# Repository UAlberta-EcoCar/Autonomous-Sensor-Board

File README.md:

# Autonomous-Sensor-Board
Connects Autonomous Sensors to the Jetson TX2 Board

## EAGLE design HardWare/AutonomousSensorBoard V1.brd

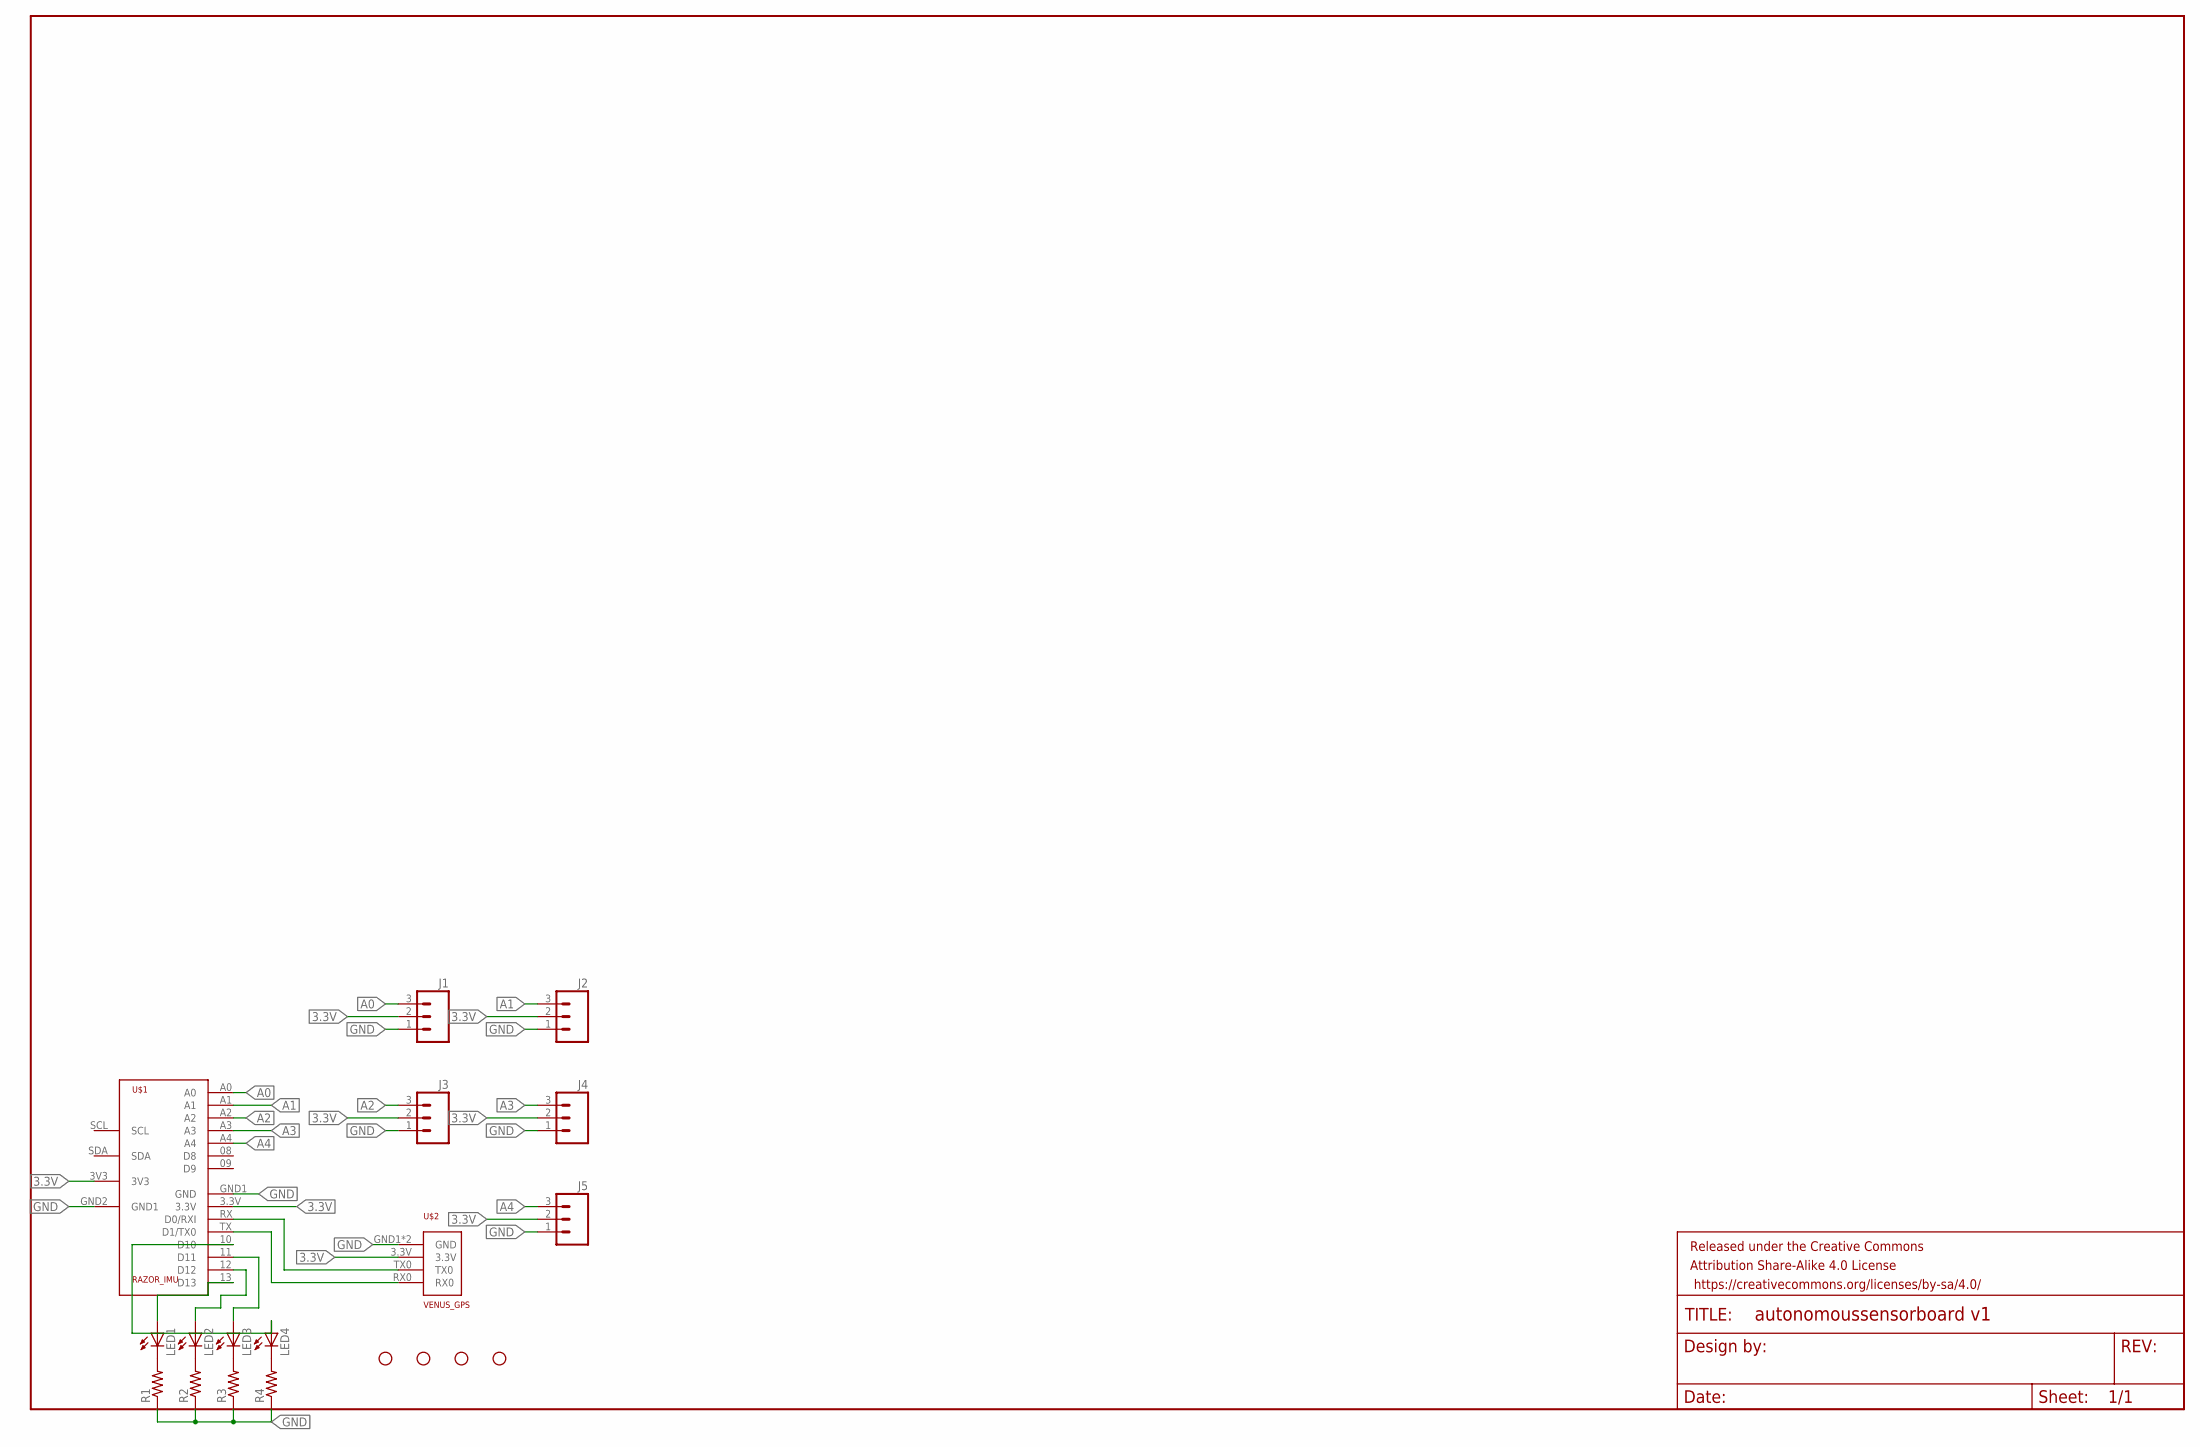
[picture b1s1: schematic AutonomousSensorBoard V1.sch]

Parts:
FRAME1: FRAME-LEDGER; CREATIVE_COMMONS
H1, H2, H3, H4: STAND-OFF
J1, J2, J3, J4, J5: M03LOCK; 1X03_LOCK
LED1, LED2, LED3, LED4: LEDCHIP-LED0805; CHIP-LED0805
R1, R2, R3, R4: R-US_M0805; M0805
U$1: RAZOR_IMU
U$2: VENUS_GPS

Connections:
3.3V: J1.2, J2.2, J3.2, J4.2, J5.2, U$1.3.3V, U$1.3V3, U$2.3.3V
A0: J1.3, U$1.A0
A1: J2.3, U$1.A1
A2: J3.3, U$1.A2
A3: J4.3, U$1.A3
A4: J5.3, U$1.A4
GND: J1.1, J2.1, J3.1, J4.1, J5.1, R1.1, R2.1, R3.1, R4.1, U$1.GND1 (GND), U$1.GND2 (GND1), U$2.GND1 (GND), U$2.GND2 (GND)
unnamed: U$1.RX (D0/RXI), U$2.TX0
unnamed: U$1.TX (D1/TX0), U$2.RX0
unnamed: LED1.C, R1.2
unnamed: LED2.C, R2.2
unnamed: LED4.C, R4.2
unnamed: LED3.C, R3.2
unnamed: LED2.A, U$1.12 (D12)
unnamed: LED1.A, U$1.13 (D13)
unnamed: LED3.A, U$1.11 (D11)
unnamed: LED4.A, U$1.10 (D10)

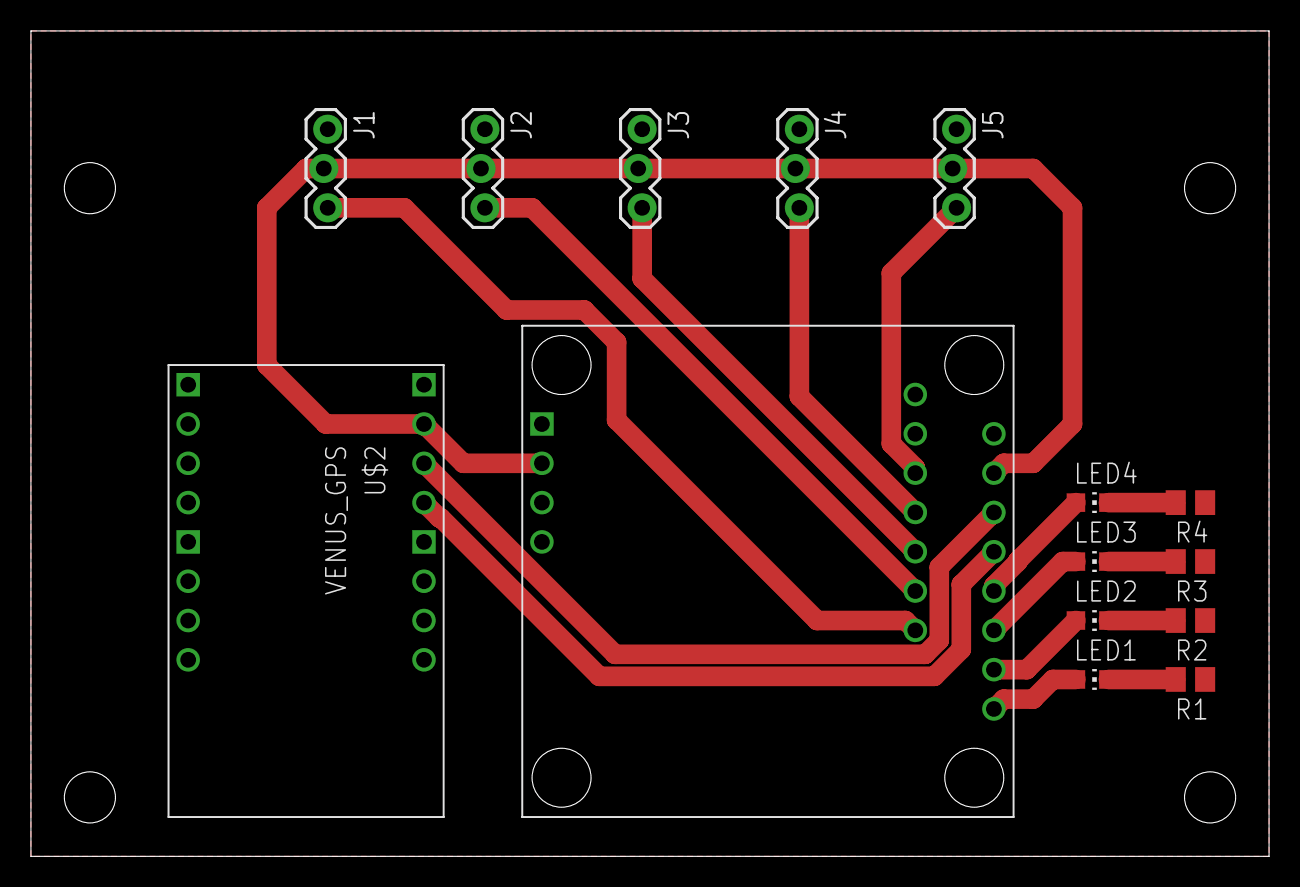
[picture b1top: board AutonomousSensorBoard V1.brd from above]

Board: 2 copper layers, 80.0 x 53.3 mm, 20 parts (0 on the bottom side), 17 nets.

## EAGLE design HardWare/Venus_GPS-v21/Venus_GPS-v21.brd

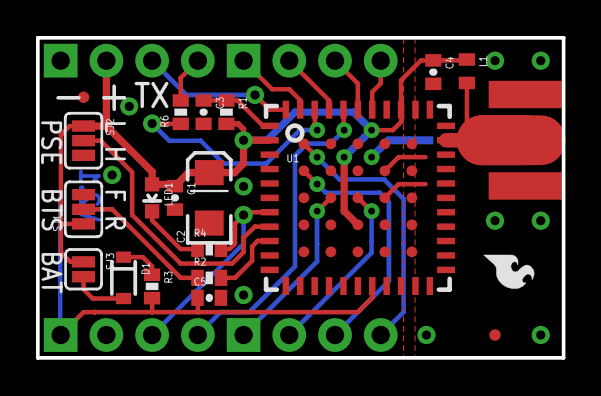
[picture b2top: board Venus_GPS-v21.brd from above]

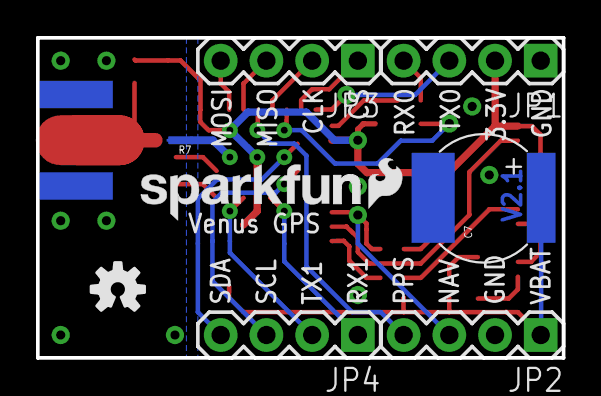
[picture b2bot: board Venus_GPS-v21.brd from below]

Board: 2 copper layers, 29.2 x 17.8 mm, 31 parts (9 on the bottom side), 25 nets.

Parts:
C1, C5: 0.1uF; 0402-CAP
C2: 10uF; EIA3216
C3: 1uF; 0402-CAP
C4: 22pF; 0402-CAP
C7: DNP; EN_J2
D1: BAS16; SOD-323
JP1: MAIN; 1X04
JP2: MISC; 1X04
JP3: SPI; 1X04
JP4: AUX; 1X04
JP5: SMA_EDGE; SMA-EDGE
JP6, JP7: FIDUCIALUFIDUCIAL; MICRO-FIDUCIAL
L1: 33nH; C0402
LED1: Red; LED-0603
LOGO1, LOGO2: LOGO-SFESK; SFE-LOGO-FLAME
LOGO3: LOGO-SFENW2; SFE-NEW-WEB
R1: 33k; 0402-RES
R2: 10k; 0402-RES
R3, R4: 330; 0402-RES
R6: 10K; 0402-RES
R7: 0; GND-JUMP
SJ1: BTS; SJ_3_PASTE2&3
SJ2: PSE; SJ_3_PASTE2&3
SJ3: BAT; SJ_2S
U1: VENUS638FLPX-L; VENUS638FLPX
U$4: OSHW-LOGOS; OSHW-LOGO-S
U$5: CREATIVE_COMMONS

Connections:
3.3V: C1.1, C2.A, C4.1, JP1.2, L1.1, LED1.A, R1.2, SJ1.1, SJ2.1, SJ3.1, U1.2, U1.36, U1.58
ANT: JP5.SIG, L1.2, U1.32
BOOT_SEL: R2.2, U1.9
CLK: JP3.2, U1.41
CS: JP3.1, U1.43
GND: C1.2, C2.C, C3.2, C5.2, C7.-, JP1.1, JP2.2, R7.1, SJ1.3, SJ2.3, U1.10, U1.11, U1.15, U1.19, U1.49, U1.60, U1.64
MISO: JP3.3, U1.39
MOSI: JP3.4, U1.38
unnamed: LED1.C, R4.1
unnamed: R2.1, SJ1.2
unnamed: D1.1, R3.1
unnamed: D1.2, SJ3.2
NAV: JP2.3, R4.2, U1.7
PPS: JP2.4, U1.40
PSE_SEL: SJ2.2, U1.8
RFGND: C4.2, JP5.GND@0, JP5.GND@1, JP5.GND@2, JP5.GND@3, R7.2, U1.21, U1.22, U1.24, U1.25, U1.27, U1.28, U1.29, U1.31, U1.33, U1.61, U1.62, U1.65, U1.69
RSTN: C3.1, R1.1, U1.1
RX0: R6.1, U1.42
RX1: JP4.1, U1.52
RX01: JP1.4, R6.2
SCL: JP4.3, U1.46
SDA: JP4.4, U1.45
TX0: JP1.3, U1.44
TX1: JP4.2, U1.57
VBAT: C5.1, C7.+, JP2.1, R3.2, U1.18

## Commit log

2017-12-02 Found some libraries, starting to test
2017-12-29 Started EAGLE Design
    made libraries for gps and IMUs
2017-12-29 gerbers generated
2018-01-20 adding platform io firmware project
2018-02-02 Add kalman filtering library

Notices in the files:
parts and their libraries:
SparkFun-Connectors: Licensing: Creative Commons ShareAlike 4.0 International - https://creativecommons.org/licenses/by-sa/4.0
SparkFun-Aesthetics: Released under the Creative Commons Attribution Share-Alike 4.0 License
SparkFun-Aesthetics: https://creativecommons.org/licenses/by-sa/4.0
